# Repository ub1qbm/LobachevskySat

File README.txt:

Семейство Шмуклеров производило гвозди на протяжении всей жизни, прадедушка был гвоздоделом, дедушка, потом папа. Когда они приватизировали этот завод по производству гвоздей, папа говорит сыну:

— «Фима, я 30 лет на производстве и ни разу не был в отпуске… Давай ты останься за директора, а я хоть на месяц уеду с мамой, отдохну …»
— «Папа, я же не специалист, я маркетолог, я рекламист!»
— «Сыночка, у нас полные склады гвоздей! Ты только поруководи, попродавай эти гвозди, а я через месяц вернусь — и всё будет в порядке!»

Сын остался, папа уехал. Через две недели папа получает телеграмму: «Папа срочно выезжай гвозди закончились».
Папа приезжает:
— «Как — закончились?!»
— «Папа, я дал рекламу…»
— «А ну, покажи!»Сын показывает макет биллборда; на нем изображен Иисус Христос, прибитый к кресту, и надпись:
«Гвозди Шмуклера — держатся уже 2000 лет».

Папа говорит:
— «Фима! Ты, конечно, идеальный маркетолог, но ты идиот! Как можно было изображать Иисуса Христа на рекламе? Мало нас, евреев, били, погромы устраивали? Немедленно снять!!!»

Папа дал команду, нарастили производство, Фима снял рекламу, папа уехал отдыхать дальше.

Через две недели опять приходит срочная телеграмма:
— «Папа срочно вылетай и эти гвозди закончились».
— «Что, опять реклама?»
— «Да, только успокойся — никакого Иисуса Христа, всё как ты просил».Папа смотрит на макет биллборда — там изображение пустого креста, без Иисуса, и надпись:
«Если бы у вас были гвозди Шмуклера…»

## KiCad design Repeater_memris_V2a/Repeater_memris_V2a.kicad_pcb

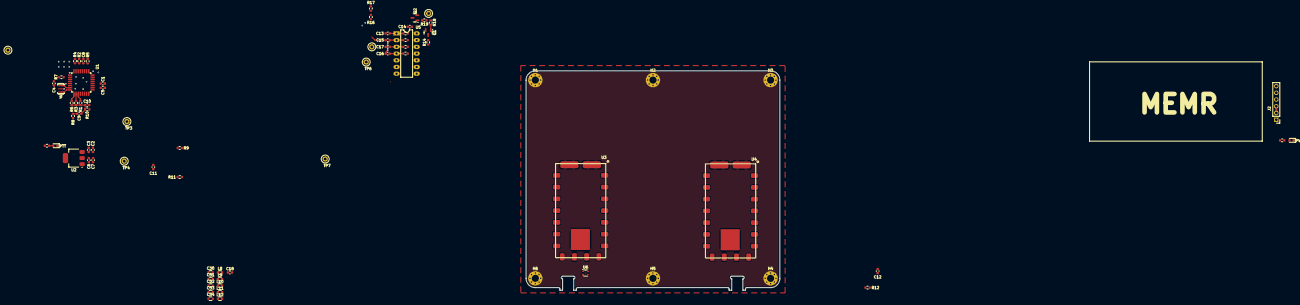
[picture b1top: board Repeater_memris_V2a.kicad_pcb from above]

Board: 4 copper layers, 96.0 x 83.0 mm, 76 parts (0 on the bottom side), 38 nets.

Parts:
C1, C2, C4, C5, C6, C8, C10, C14, C18: 100nF; C_0603_1608Metric
C3, C7: 10uF; C_0603_1608Metric
C9, C13, C15, C16, C17: 4.7uF; C_0603_1608Metric
C11, C12: 1uF; C_0603_1608Metric
C30, C34: 15pF; C_0603_HS
C31, C33: 1.8pF; C_0603_HS
C32: 10pF; C_0603_HS
D1, D2: LED; LED_0603_1608Metric
H1, H2, H3, H4, H5, H6: MountingHole_Pad; MountingHole_2.7mm_Pad_Via
J2: Conn_01x06_Socket; PinHeader_1x06_P2.54mm_Vertical
L8, L12: 22nH; L_0603_HS
L9, L10, L11: 8.2nH; L_0603_HS
Q1, Q2: MMBT2222A; SOT-23
R1, R2, R4, R5, R13, R14, R15, R20, R23: 1K; R_0603_1608Metric
R3: 2K; R_0603_1608Metric
R6: 4K; R_0603_1608Metric
R7: 8K; R_0603_1608Metric
R8: *R; R_0603_1608Metric
R9, R11, R12: 0R; R_0603_1608Metric
R10: 270R; R_0603_1608Metric
R16, R17: 150K; R_0603_1608Metric
R18, R19, R21, R22: 220R; R_0603_1608Metric
TP3, TP4, TP5, TP6, TP7, TP13, TP15: TestPoint; TestPoint_Loop_D1.80mm_Drill1.0mm_Beaded
U1: ATmega328-A; TQFP-32_7x7mm_P0.8mm
U2: AMS1117-3.3; SOT-223-3_TabPin2
U3: SA868-U; SA868
U4: SA868-V; SA868
U5: 4016; DIP-14_W7.62mm_LongPads
U6: SPF5043Z; SOT-343_SC-70-4
Y1: Crystal_GND2; CSTCE16M0V53-R0

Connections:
+3.3REF: C1.2, C6.2, C7.2, R16.1, U1.20 (AREF), U2.2 (VO)
+5V: C2.2, C3.2, C11.2, C12.2, J2.2, J2.3, R5.1, R13.1, R14.1, R15.1, R20.1, R21.1, R23.1, U1.4 (VCC), U1.6 (VCC), U1.18 (AVCC), U2.3 (VI), U3.5 (PTT), U3.6 (PD), U3.8 (VDD), U4.6 (PD), U4.8 (VDD), U5.14 (VDD)
AFSK_OUT: C17.1, R8.2, TP15.1
AFSK_RX: C13.1, R16.2, R17.1, U1.23 (PC0), U3.3 (AFOUT)
CONTR: U1.12 (PB0), U5.5
GND: C1.1, C2.1, C3.1, C6.1, C7.1, C10.2, C11.1, C12.1, D1.1 (K), D2.1 (K), H1.1, H2.1, H3.1, H4.1, H5.1, H6.1, J2.1, J2.4, J2.6, Q1.2 (E), Q2.2 (E), R9.1, R10.2, R11.2, R12.2, R17.2, TP3.1, TP4.1, TP5.1, TP6.1, TP7.1, U1.3 (GND), U1.5 (GND), U1.21 (GND), U2.1 (GND), U3.9 (GND), U4.9 (GND), U5.7 (VSS), U6.2, U6.4, Y1.2
GND_RF: C30.2, C32.2, C34.2, L9.1, L10.1, L11.1
MIC_IN: C15.1, U4.18 (MIC)
unnamed: C9.2, R8.1
unnamed: C9.1, C10.1, R1.2, R3.2, R6.2, R7.2, R10.1
unnamed: C13.2, R13.2, U5.1
unnamed: C15.2, C16.1, R15.2, U5.2
unnamed: C16.2, R20.2, U5.4
unnamed: C17.2, R23.2, U5.3
unnamed: C18.1, L12.2
unnamed: C18.2, U6.3
unnamed: C30.1, C31.1, L8.2, L9.2
unnamed: C31.2, C32.1, C33.1, L10.2
unnamed: C33.2, C34.1, L11.2, L12.1
unnamed: D1.2 (A), R21.2
unnamed: D2.2 (A), R22.2
unnamed: Q1.1 (B), R18.1
unnamed: Q1.3 (C), R14.2, U5.13
unnamed: Q2.1 (B), R19.2
unnamed: R2.1, U1.30 (PD0)
unnamed: R4.1, U1.31 (PD1)
unnamed: R7.1, U1.2 (PD4)
unnamed: R6.1, U1.9 (PD5)
unnamed: R3.1, U1.10 (PD6)
unnamed: R1.1, U1.11 (PD7)
unnamed: U1.7 (XTAL1/PB6), Y1.3
unnamed: U1.8 (XTAL2/PB7), Y1.1
unnamed: C8.1, R5.2, U1.29 (~RESET/PC6)
unnamed: R11.1, U3.7 (H/L)
unnamed: R9.2, U3.18 (MIC)
unnamed: R12.1, U4.7 (H/L)
PTT: R18.2, R19.1, R22.1, TP13.1, U1.13 (PB1)
PTT_AT: Q2.3 (C), U3.1 (AFON), U4.5 (PTT)

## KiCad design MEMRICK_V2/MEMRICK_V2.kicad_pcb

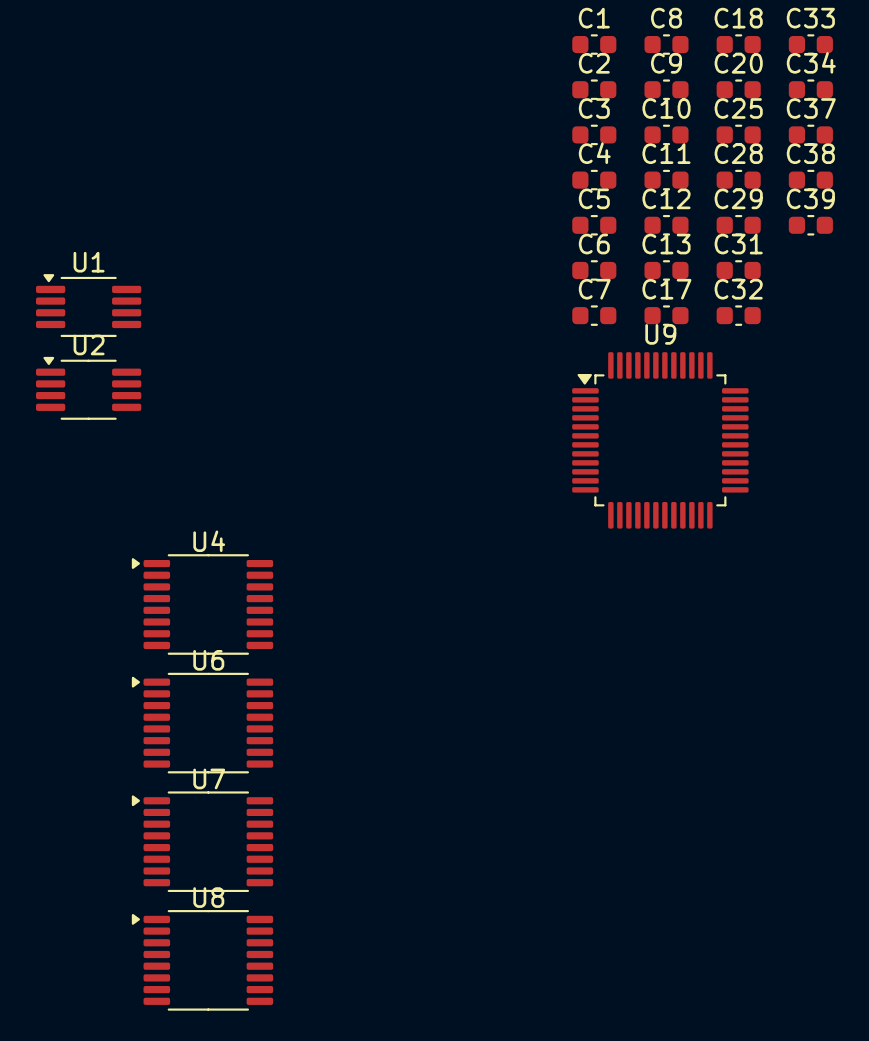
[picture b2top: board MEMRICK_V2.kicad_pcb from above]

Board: 2 copper layers, 33 parts (0 on the bottom side), 23 nets, no tracks yet.

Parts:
C1, C2, C4, C5, C6, C8, C17, C18, C20, C25, C28, C29, C31, C32, C33, C34, C37: 100n; C_0603_1608Metric
C3, C7, C9, C11, C13: 10n; C_0603_1608Metric
C10, C12: 220n; C_0603_1608Metric
C38, C39: 6.8p; C_0603_1608Metric
U1, U2: AD8616ARMZ; MSOP-8_3x3mm_P0.65mm
U4, U6, U7, U8: ADG1408YRUZ; TSSOP-16_4.4x5mm_P0.65mm
U9: STM32G431CBT6; LQFP-48_7x7mm_P0.5mm

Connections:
GND: C1.1, C2.1, C3.2, C4.1, C5.1, C6.2, C7.1, C8.1, C9.2, C10.2, C11.2, C12.1, C13.1, C17.1, C18.1, C20.1, C25.1, C28.1, C29.1, C31.1, C32.1, C33.1, C34.1, C37.1, C38.2, C39.2, U1.3 (+), U1.4 (V-), U2.8 (V+), U4.14 (GND), U6.14 (GND), U7.14 (GND), U8.14 (GND), U9.19 (VSSA), U9.23 (VSS), U9.35 (VSS), U9.47 (VSS)
unnamed: U4.15 (A2), U6.15 (A2), U7.15 (A2), U8.15 (A2)
unnamed: U4.16 (A1), U6.16 (A1), U7.16 (A1), U8.16 (A1)
unnamed: U4.1 (A0), U6.1 (A0), U7.1 (A0), U8.1 (A0)
unnamed: U4.2 (EN), U6.2 (EN)
unnamed: U7.2 (EN), U8.2 (EN)
unnamed: U1.5 (+), U9.10 (PA2)
unnamed: U9.34 (PA12), U9.39 (PA15), U9.41 (PB4)
unnamed: C9.1, U2.3 (+)
unnamed: U2.1, U2.5 (+)
unnamed: U4.8 (D), U7.8 (D)
unnamed: U6.8 (D), U8.8 (D)
unnamed: U4.6 (S3), U6.6 (S3)
unnamed: U7.5 (S2), U8.5 (S2)
unnamed: U9.9 (PA1), U9.17 (PB1)
unnamed: U9.11 (PA3), U9.14 (PA6)
unnamed: C38.1, U9.5 (PF0-OSC_IN)
unnamed: C39.1, U9.6 (PF1-OSC_OUT)
unnamed: C37.2, U9.7 (PG10-NRST)
unnamed: C18.2, C20.2, C25.2, C29.2, U9.1 (VBAT), U9.24 (VDD), U9.36 (VDD), U9.48 (VDD)
unnamed: C34.2, U9.21 (VDDA)
unnamed: C1.2, C2.2, C3.1, C4.2, C10.1, C11.1, C28.2, C32.2, U1.8 (V+), U4.13 (VDD), U6.13 (VDD), U7.13 (VDD), U8.13 (VDD)
unnamed: C5.2, C6.1, C7.2, C8.2, C12.2, C13.2, C31.2, C33.2, U2.4 (V-), U4.3 (VSS), U6.3 (VSS), U7.3 (VSS), U8.3 (VSS)

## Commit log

2024-09-15 работа на схеме и плате. Начата перерисовка схемы
2024-09-15 Реорганизация папок
2024-09-15 no message
2024-09-20 вложены документы и 3Д модели
2024-09-21 Add files via upload
    project easyeda....f*ck!!!
2024-09-24 MEMRICK_V2 added
2024-09-24 Reapeter_memris_V2a added
2024-10-01 sch pcb update
2024-10-01 Revert "sch pcb update"
    This reverts commit 82fe7de560fbc9173e196ee1871e922f74af1bd5.
2024-10-01 Reapply "sch pcb update"
    This reverts commit 494b07078b51d12a338e7602947645be1da97d00.
